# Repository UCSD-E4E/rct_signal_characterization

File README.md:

# RCTSpring2017

General Overview:

Researchers will often put radio collars on animals before releasing them to gather valuable behavioral data. The researchers will periodically track the animal positions and eventually attempt to recover the radio collars. In some places, such as the Cayman Islands and the Dominican Republic, the wilderness is tough terrain to traverse potentially taking more than an hour to walk a mile. The Radio Collar Tracker project is designed to address this terrestrial problem by taking to the skies and mounting an antenna onto a quadcopter that is then autonomously flown over the area suspected of containing the animals of interest. The system on the copter listens and aggregates pings transmitted by the animals’ radio collars and triangulates their position using GPS data. This allows the researchers to gather the same data while avoiding treacherous terrain in environments remote to any emergency medical services.

This repo contains any and all CSE 145/237D project code utilized during UCSD's academic spring quarter 2017 to improve upon the RCT design. The following improvements will be implemented:

(1) Integrate and parse an external Ublox m8n GPS module into the payload of a new aerial platform, the 3DR Solo. This task will comprise of writing a python script for the Intel Joule, a Linux microcomputer. 

(2) Design a new user interface for starting and stopping data logging with visual indicators of 3D GPS fix. This task will comprise of writing a bash script for the Intel Joule, as well as a script for an external web GUI. The scripts for this section of the project can be found under the scripts subfolder of the repository.

(3) Emulate a radio collar’s power output in various waveforms using a USRP. This task will comprise of utilizing and implementing the open source SDR library GNURadio.

The team contains four members this quarter. Samuel Vineyard is working on (1). Thomas An is working on (2). Naveen Ketagoda and Daniel Knapp are working on (3).

This repo will push its final software deliverables to the main E4E Radio Collar Tracker repo: https://github.com/UCSD-E4E/radio_collar_tracker_drone. The following open source repos are used in this project:

(1) Ublox binary data parsing: https://github.com/tridgeIn/pyUblox

More information about the project can be found at the UCSD E4E website: http://e4e.ucsd.edu/radio-collar-tracker

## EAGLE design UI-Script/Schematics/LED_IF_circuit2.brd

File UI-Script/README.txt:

To integrate these series of the script into the project, 

1) rct_service.sh serves as the old rctstart.sh
	This services will start with boot and upon start
	will call rct_status.sh

2) rct_status.sh and rct_run.sh are two parts of the finite 
	state machine described. rct_status.sh will perform all of
	the status checks in parallel and upon complete checks it will
	terminate and call rct_run then wait for the users start command.
	If the checks fail, the script will throw error and all checks will cease

	To integrate with the original E4E RCT project, rct_status and rct_run
	will replace the old rctrun.sh

LED Interface:
Status Check PIN and LED Mapping:
1) Sane output Directory 		GPIO Pin 12		LED GREEN
2) Writable Output Directory	GPIO Pin 14		LED YELLOW
3) Verify SDR					GPIO Pin 16		LED HYPERRED (orange)
4) Available Disk Space			GPIO Pin 18		LED BRIGHT RED
5) GPS 3D Fix					GPIO Pin 20		LED BLUE

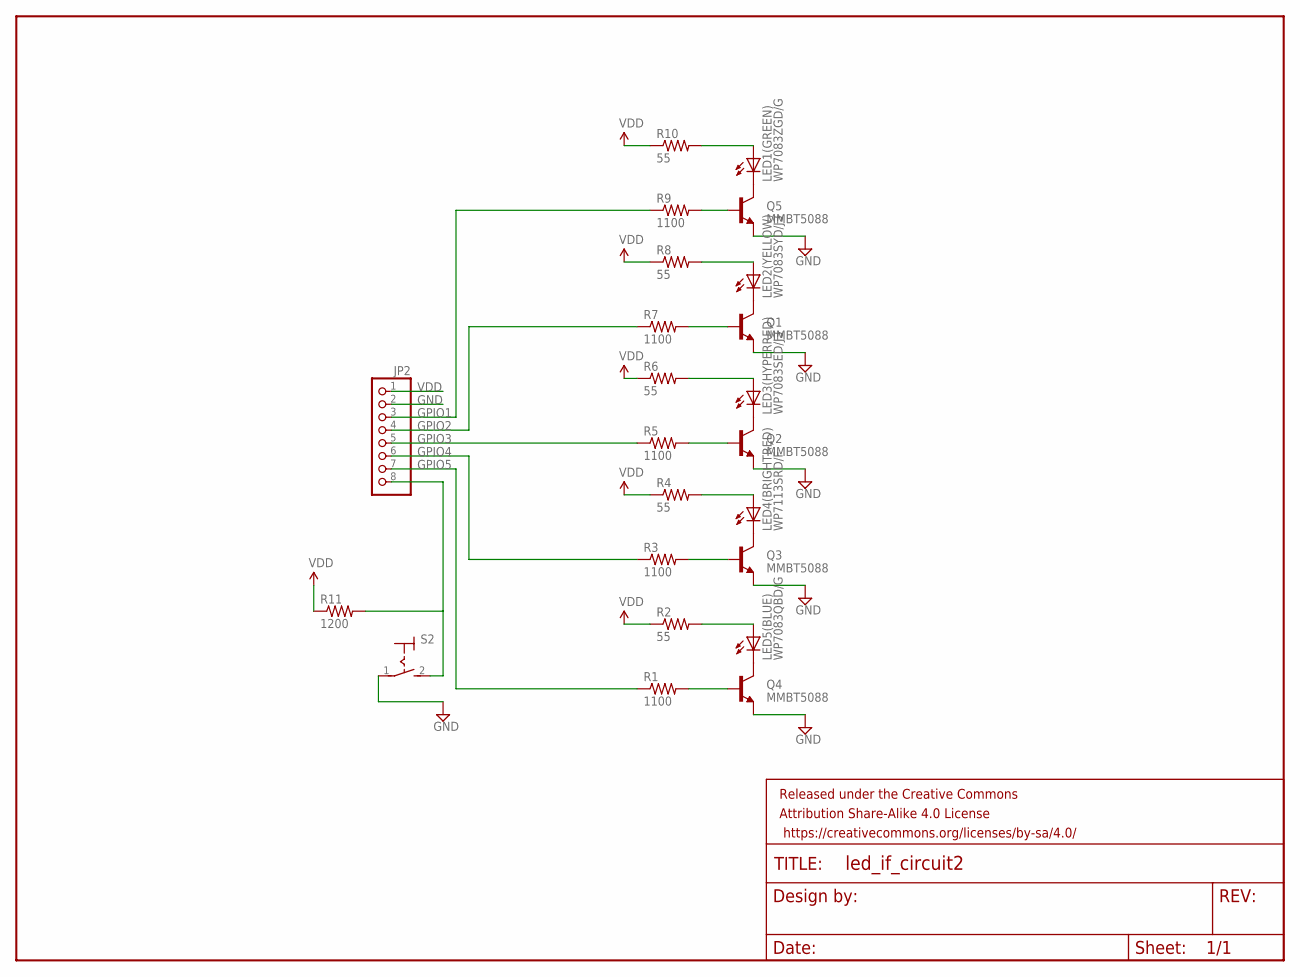
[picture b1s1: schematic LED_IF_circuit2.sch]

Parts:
FRAME1: FRAME-LETTERNO_PACKAGE; DUMMY
JP2: PINHD-1X8; 1X08
LED1(GREEN): WP7083ZGD/G; LED5MM
LED2(YELLOW): WP7083SYD/J3; LED5MM
LED3(HYPERRED): WP7083SED/J3; LED5MM
LED4(BRIGHTRED): WP7113SRD/F; LED5MM
LED5(BLUE): WP7083QBD/G; LED5MM
Q1, Q2, Q3, Q4, Q5: MMBT5088; SOT23-3
R1, R3, R5, R7, R9: 1100; 0603-RES
R2, R4, R6, R8, R10: 55; 0603-RES
R11: 1200; 0603-RES
S2: MS243TMS6T5B2M2RETMS6T5B2M2RE; MS243

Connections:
GND: JP2.2, Q1.2 (E), Q2.2 (E), Q3.2 (E), Q4.2 (E), Q5.2 (E), S2.1
GPIO1: JP2.3, R9.1
GPIO2: JP2.4, R7.1
GPIO3: JP2.5, R5.1
GPIO4: JP2.6, R3.1
GPIO5: JP2.7, R1.1
unnamed: LED1(GREEN).K (C), Q5.3 (C)
unnamed: LED2(YELLOW).K (C), Q1.3 (C)
unnamed: LED3(HYPERRED).K (C), Q2.3 (C)
unnamed: LED4(BRIGHTRED).K (C), Q3.3 (C)
unnamed: LED5(BLUE).K (C), Q4.3 (C)
unnamed: LED1(GREEN).A, R10.2
unnamed: Q5.1 (B), R9.2
unnamed: LED2(YELLOW).A, R8.2
unnamed: Q1.1 (B), R7.2
unnamed: LED5(BLUE).A, R2.2
unnamed: Q3.1 (B), R3.2
unnamed: LED4(BRIGHTRED).A, R4.2
unnamed: Q2.1 (B), R5.2
unnamed: LED3(HYPERRED).A, R6.2
unnamed: Q4.1 (B), R1.2
unnamed: JP2.8, R11.2, S2.2 (S)
VDD: JP2.1, R2.1, R4.1, R6.1, R8.1, R10.1, R11.1

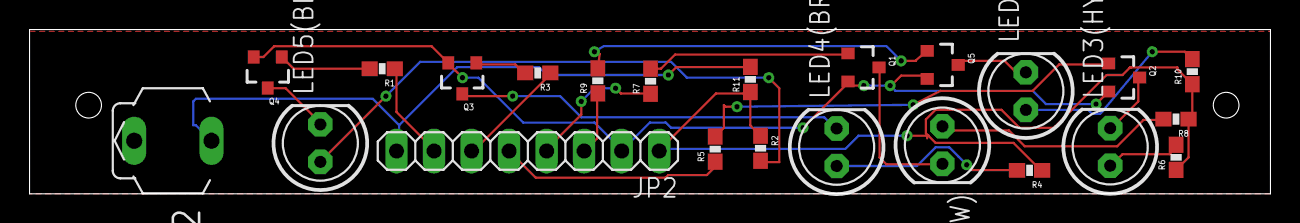
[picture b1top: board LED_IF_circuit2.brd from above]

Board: 2 copper layers, 84.0 x 11.1 mm, 24 parts (0 on the bottom side), 23 nets.

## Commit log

2017-05-04 Included improvement task description.
2017-05-04 Formatting updates
2017-05-04 More formatting updates
2017-05-04 Added some collar emulator files
2017-05-04 Update README.md
    Added a revised abstract or project overview.
2017-05-04 Update README.md
    Formatting
2017-05-04 Update README.md
    Added team members
2017-05-04 UI SCRIPT
2017-05-05 Added GPS fix parsing script and sample data to test with
2017-05-05 Removed print statements
2017-05-05 Removed unnecessary imports and lines
2017-05-10 Added new gps logging script, includes 3 Fix logging
2017-05-10 temp
2017-05-10 Added archive and sampleData directory
2017-05-10 Created separate script for 3D fix checking
2017-05-10 Fixed status check to perform at the start. Status check keeps running until GPS fix found or error thrown
2017-05-16 Updated a bit more
2017-05-17 Modified scrips to pass 0/1's to each other and broke ui-script into rct_status and rct_run, which are initiated by rct_service
2017-05-17 Adding vx, vy, vz, heading, global timestamp
2017-05-18 Added Presentations directory like Prof Kastner wanted.
2017-05-18 milestones and updates
2017-05-23 Condensed methods, organized folders
2017-05-27 Added modified version of ublox.py from pyUblox library
2017-05-30 Added schematic for EAGLE along with library files
2017-05-31 GPIO and LED files
2017-05-31 Code for analyzing a signal (specifically for a pulse like a radio collar) recorded as complex values in gnuradio. Prints average amplitude and pulse width in number of samples. Also plots the record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
2017-05-31 Document on integration
2017-05-31 connected and routed PCB + schematics
2017-05-31 Switched to thru hole
2017-05-31 GND copper pours added
2017-05-31 Added PVT message to ublox.py library
2017-06-01 PCB update
2017-06-01 Changed message type to NAV-PVT
2017-06-09 no error DRC
2017-06-09 changed m2 hole a bit to be 4mm from top, since dimensions are 11x85mm. That way the switch is on the far end and more accessible under the slanted overhead from the 3DR
2017-06-09 Added PHP file that generates initial page.
    Still need javascript for live page updates, formatting and labeling of status/toggle switch icons.
2017-06-09 Images for web interface.
2017-06-09 javascript added
2017-06-09 name change
2017-06-09 web interface LED function
2017-06-10 Web interface now has full backend functionality for status checks and user input for start/stop.
2017-06-10 Changed to update.js
2017-06-10 added demo py script status_checking.py
2017-06-11 LED pin assignments and colors
2017-06-16 Adding collar emulator signal analysis and fft python files
2017-06-16 Rearranged the analysis scripts to an analysis folder
2017-06-21 PWM Block files
2017-06-21 README.md for PWM block
2019-10-24 Initial version - MWE
2019-11-14 Fixed FFTW calls
2020-04-07 rct_analysis dump
2020-04-12 Removed unneeded data"
2020-04-12 Added Path Planning and Threshold Analysis files
2020-09-23 Initial commit, full ping detection
2020-10-02 Updated to demonstrate below noise floor
2020-10-08 Added output and final ping
2022-07-23 Update gitignore
2022-07-23 Updating waterfall analysis
2023-02-19 multi FT spectral generation for signal Tx-Rx
    version 1
2023-02-20 4 sample ft generations, from multi script
    only "prez_ftser_sigs_multi.py"

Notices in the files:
parts and their libraries:
SparkFun-Aesthetics: Licensing: Creative Commons ShareAlike 4.0 International - https://creativecommons.org/licenses/by-sa/4.0
SparkFun-Aesthetics: Released under the Creative Commons Attribution Share-Alike 4.0 License
SparkFun-Aesthetics: https://creativecommons.org/licenses/by-sa/4.0
